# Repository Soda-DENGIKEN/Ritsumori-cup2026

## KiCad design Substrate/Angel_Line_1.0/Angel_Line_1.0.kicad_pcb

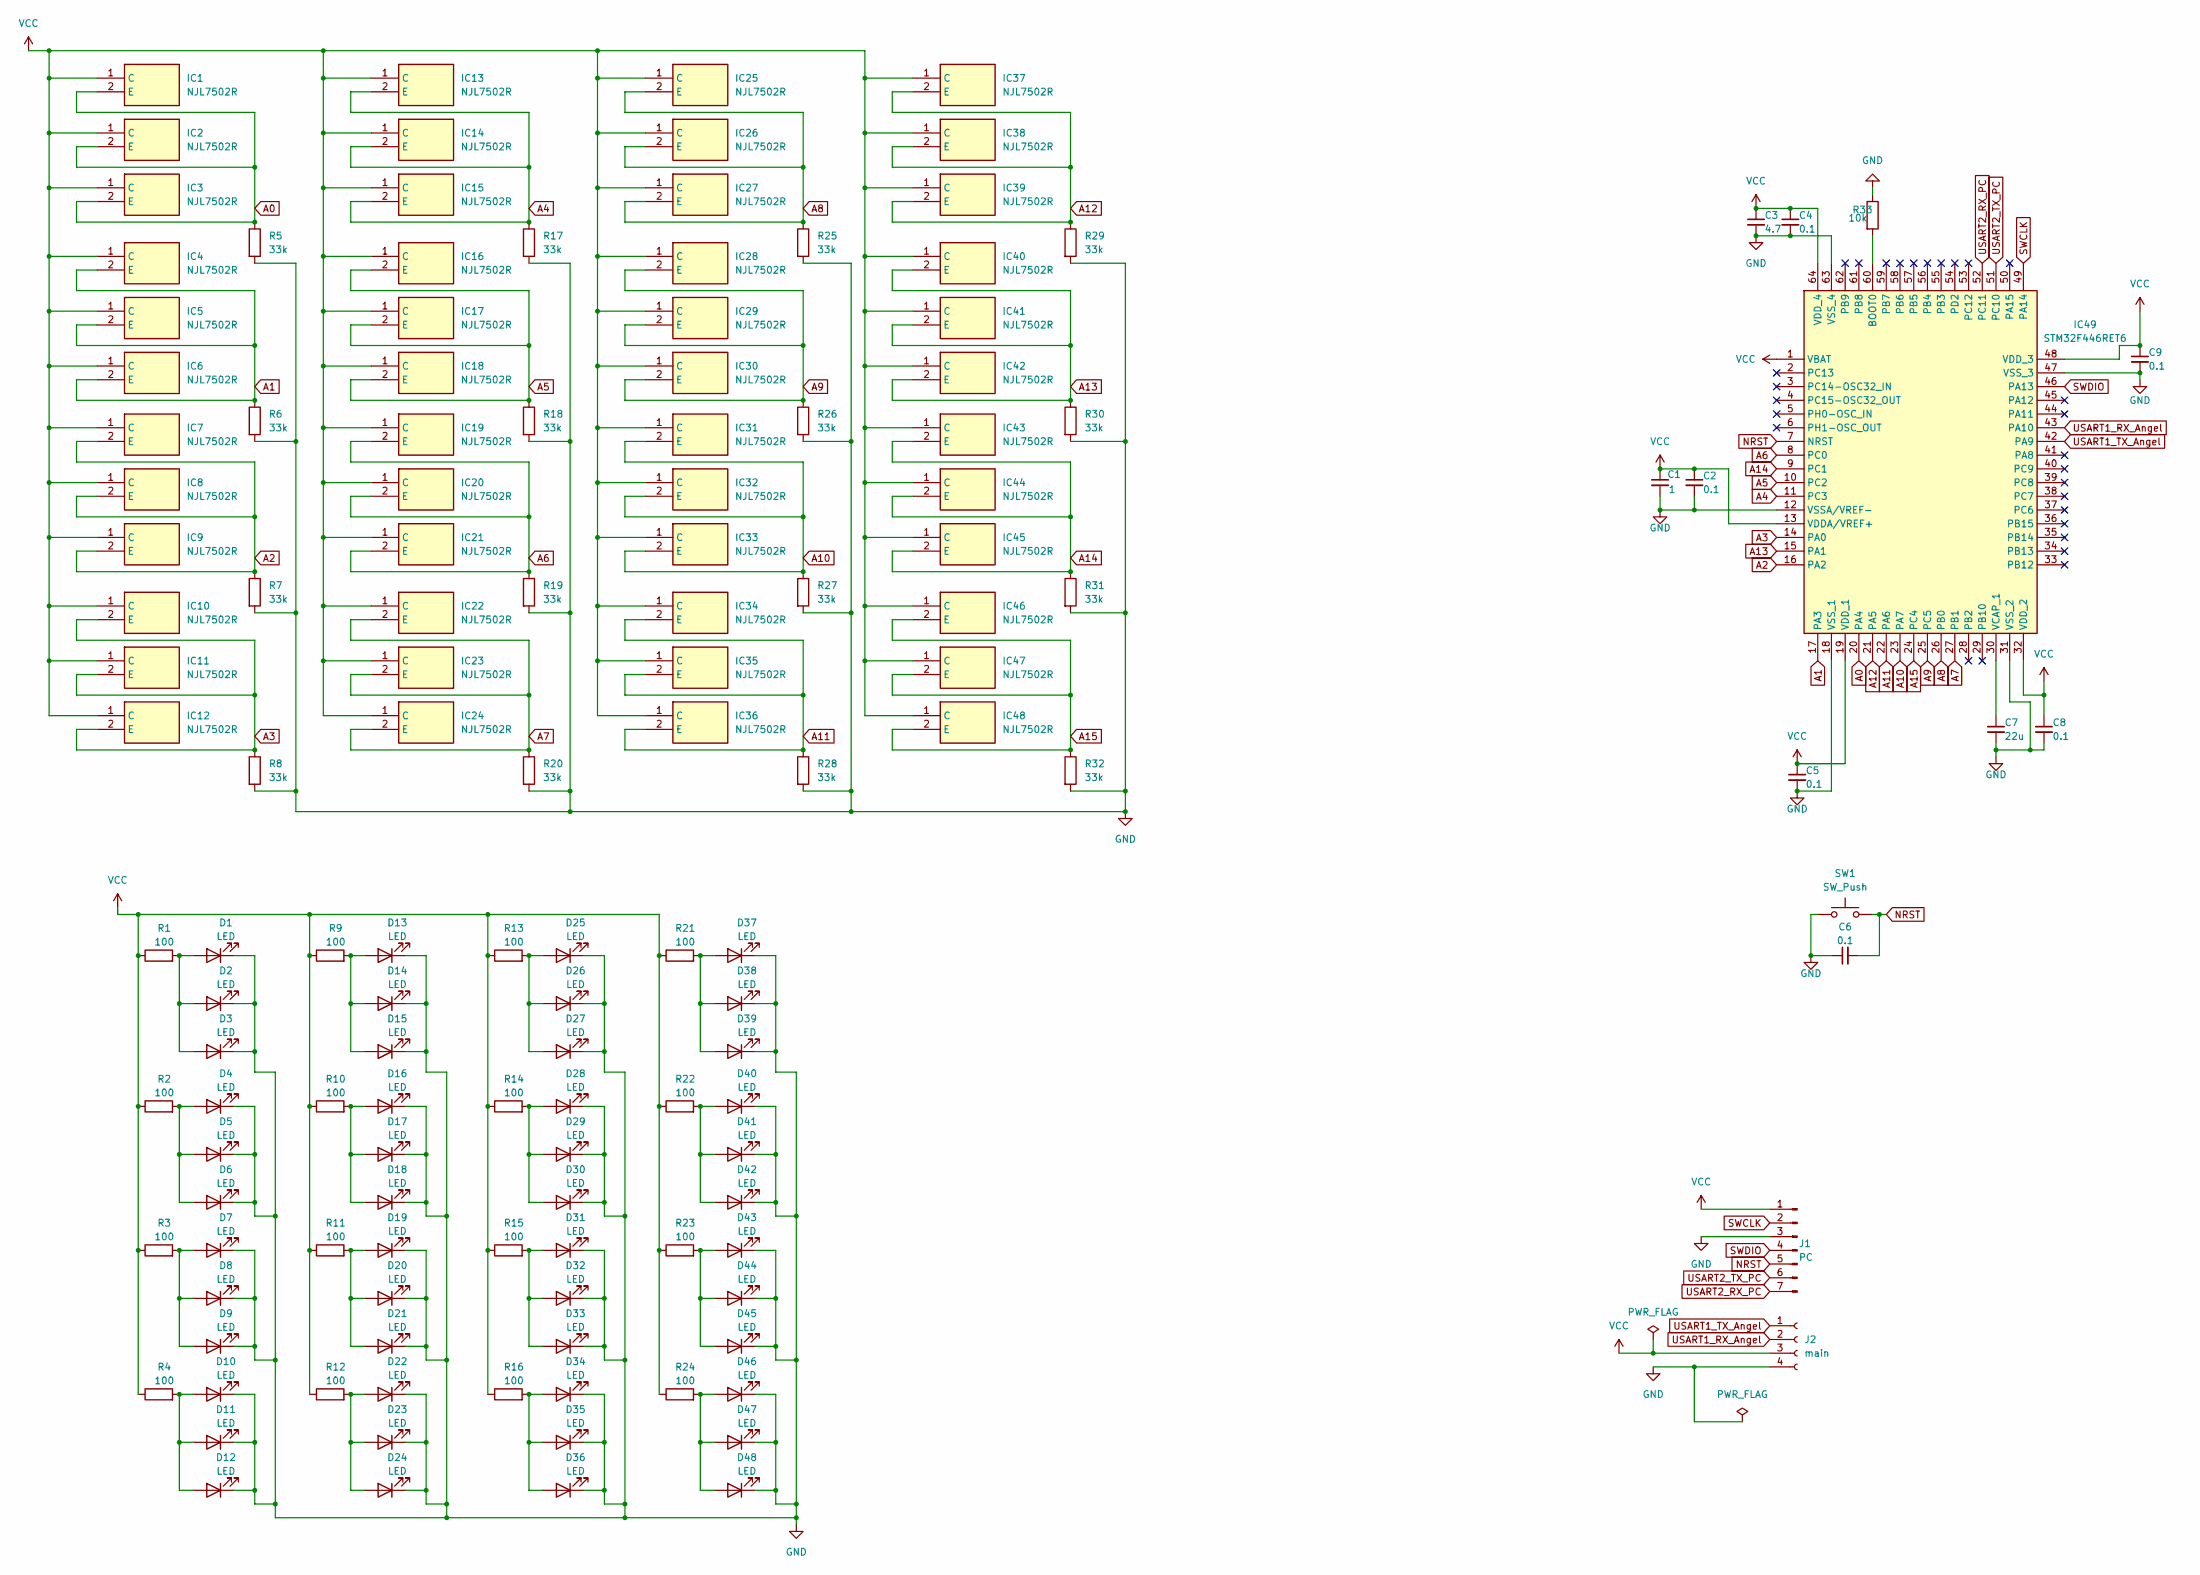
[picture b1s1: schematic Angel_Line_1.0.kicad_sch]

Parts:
C1: 1; C_0603_1608Metric
C2, C4, C5, C6, C8, C9: 0.1; C_0603_1608Metric
C3: 4.7; C_0603_1608Metric
C7: 22u; C_0603_1608Metric
D1, D2, D3, D4, D5, D6, D7, D8, D9, D10, D11, D12, D13, D14, D15, D16, D17, D18, D19, D20, D21, D22, D23, D24, D25, D26, D27, D28, D29, D30, D31, D32, D33, D34, D35, D36, D37, D38, D39, D40, D41, D42, D43, D44, D45, D46, D47, D48: LED; LED_0603_1608Metric_Pad1.05x0.95mm_HandSolder
IC1, IC2, IC3, IC4, IC5, IC6, IC7, IC8, IC9, IC10, IC11, IC12, IC13, IC14, IC15, IC16, IC17, IC18, IC19, IC20, IC21, IC22, IC23, IC24, IC25, IC26, IC27, IC28, IC29, IC30, IC31, IC32, IC33, IC34, IC35, IC36, IC37, IC38, IC39, IC40, IC41, IC42, IC43, IC44, IC45, IC46, IC47, IC48: NJL7502R; Manufacturer_Part_Number NJL7502R
IC49: STM32F446RET6; LQFP-64_10x10mm_P0.5mm; Manufacturer_Part_Number STM32F446RET6; Mouser Part Number 511-STM32F446RET6
J1: PC; PinHeader_1x07_P2.54mm_Vertical
J2: main; JST_XH_B4B-XH-A_1x04_P2.50mm_Vertical
R1, R2, R3, R4, R9, R10, R11, R12, R13, R14, R15, R16, R21, R22, R23, R24: 100; R_0603_1608Metric_Pad0.98x0.95mm_HandSolder
R5, R6, R7, R8, R17, R18, R19, R20, R25, R26, R27, R28, R29, R30, R31, R32: 33k; R_0603_1608Metric_Pad0.98x0.95mm_HandSolder
R33: 10k; R_0603_1608Metric
SW1: SW_Push; SKRPABE010

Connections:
A0: IC1.2 (E), IC2.2 (E), IC3.2 (E), IC49.20 (PA4), R5.1
A1: IC4.2 (E), IC5.2 (E), IC6.2 (E), IC49.17 (PA3), R6.1
A2: IC7.2 (E), IC8.2 (E), IC9.2 (E), IC49.16 (PA2), R7.1
A3: IC10.2 (E), IC11.2 (E), IC12.2 (E), IC49.14 (PA0), R8.1
A4: IC13.2 (E), IC14.2 (E), IC15.2 (E), IC49.11 (PC3), R17.1
A5: IC16.2 (E), IC17.2 (E), IC18.2 (E), IC49.10 (PC2), R18.1
A6: IC19.2 (E), IC20.2 (E), IC21.2 (E), IC49.8 (PC0), R19.1
A7: IC22.2 (E), IC23.2 (E), IC24.2 (E), IC49.27 (PB1), R20.1
A8: IC25.2 (E), IC26.2 (E), IC27.2 (E), IC49.26 (PB0), R25.1
A9: IC28.2 (E), IC29.2 (E), IC30.2 (E), IC49.25 (PC5), R26.1
A10: IC31.2 (E), IC32.2 (E), IC33.2 (E), IC49.23 (PA7), R27.1
A11: IC34.2 (E), IC35.2 (E), IC36.2 (E), IC49.22 (PA6), R28.1
A12: IC37.2 (E), IC38.2 (E), IC39.2 (E), IC49.21 (PA5), R29.1
A13: IC40.2 (E), IC41.2 (E), IC42.2 (E), IC49.15 (PA1), R30.1
A14: IC43.2 (E), IC44.2 (E), IC45.2 (E), IC49.9 (PC1), R31.1
A15: IC46.2 (E), IC47.2 (E), IC48.2 (E), IC49.24 (PC4), R32.1
GND: C1.2, C2.2, C3.2, C4.2, C5.2, C6.1, C7.2, C8.2, C9.2, D1.1 (K), D2.1 (K), D3.1 (K), D4.1 (K), D5.1 (K), D6.1 (K), D7.1 (K), D8.1 (K), D9.1 (K), D10.1 (K), D11.1 (K), D12.1 (K), D13.1 (K), D14.1 (K), D15.1 (K), D16.1 (K), D17.1 (K), D18.1 (K), D19.1 (K), D20.1 (K), D21.1 (K), D22.1 (K), D23.1 (K), D24.1 (K), D25.1 (K), D26.1 (K), D27.1 (K), D28.1 (K), D29.1 (K), D30.1 (K), D31.1 (K), D32.1 (K), D33.1 (K), D34.1 (K), D35.1 (K), D36.1 (K), D37.1 (K), D38.1 (K), D39.1 (K), D40.1 (K), D41.1 (K), D42.1 (K), D43.1 (K), D44.1 (K), D45.1 (K), D46.1 (K), D47.1 (K), D48.1 (K), IC49.12 (VSSA/VREF-), IC49.18 (VSS_1), IC49.31 (VSS_2), IC49.47 (VSS_3), IC49.63 (VSS_4), J1.3, J2.4, R5.2, R6.2, R7.2, R8.2, R17.2, R18.2, R19.2, R20.2, R25.2, R26.2, R27.2, R28.2, R29.2, R30.2, R31.2, R32.2, R33.1, SW1.1
NRST: C6.2, IC49.7 (NRST), J1.5, SW1.2
unnamed: D1.2 (A), D2.2 (A), D3.2 (A), R1.2
unnamed: D4.2 (A), D5.2 (A), D6.2 (A), R2.2
unnamed: D7.2 (A), D8.2 (A), D9.2 (A), R3.2
unnamed: D10.2 (A), D11.2 (A), D12.2 (A), R4.2
unnamed: D13.2 (A), D14.2 (A), D15.2 (A), R9.2
unnamed: D16.2 (A), D17.2 (A), D18.2 (A), R10.2
unnamed: D19.2 (A), D20.2 (A), D21.2 (A), R11.2
unnamed: D22.2 (A), D23.2 (A), D24.2 (A), R12.2
unnamed: D25.2 (A), D26.2 (A), D27.2 (A), R13.2
unnamed: D28.2 (A), D29.2 (A), D30.2 (A), R14.2
unnamed: D31.2 (A), D32.2 (A), D33.2 (A), R15.2
unnamed: D34.2 (A), D35.2 (A), D36.2 (A), R16.2
unnamed: D37.2 (A), D38.2 (A), D39.2 (A), R21.2
unnamed: D40.2 (A), D41.2 (A), D42.2 (A), R22.2
unnamed: D43.2 (A), D44.2 (A), D45.2 (A), R23.2
unnamed: D46.2 (A), D47.2 (A), D48.2 (A), R24.2
unnamed: IC49.60 (BOOT0), R33.2
unnamed: C7.1, IC49.30 (VCAP_1)
SWCLK: IC49.49 (PA14), J1.2
SWDIO: IC49.46 (PA13), J1.4
USART1_RX_Angel: IC49.43 (PA10), J2.2
USART1_TX_Angel: IC49.42 (PA9), J2.1
USART2_RX_PC: IC49.52 (PC11), J1.7
USART2_TX_PC: IC49.51 (PC10), J1.6
VCC: C1.1, C2.1, C3.1, C4.1, C5.1, C8.1, C9.1, IC1.1 (C), IC2.1 (C), IC3.1 (C), IC4.1 (C), IC5.1 (C), IC6.1 (C), IC7.1 (C), IC8.1 (C), IC9.1 (C), IC10.1 (C), IC11.1 (C), IC12.1 (C), IC13.1 (C), IC14.1 (C), IC15.1 (C), IC16.1 (C), IC17.1 (C), IC18.1 (C), IC19.1 (C), IC20.1 (C), IC21.1 (C), IC22.1 (C), IC23.1 (C), IC24.1 (C), IC25.1 (C), IC26.1 (C), IC27.1 (C), IC28.1 (C), IC29.1 (C), IC30.1 (C), IC31.1 (C), IC32.1 (C), IC33.1 (C), IC34.1 (C), IC35.1 (C), IC36.1 (C), IC37.1 (C), IC38.1 (C), IC39.1 (C), IC40.1 (C), IC41.1 (C), IC42.1 (C), IC43.1 (C), IC44.1 (C), IC45.1 (C), IC46.1 (C), IC47.1 (C), IC48.1 (C), IC49.1 (VBAT), IC49.13 (VDDA/VREF+), IC49.19 (VDD_1), IC49.32 (VDD_2), IC49.48 (VDD_3), IC49.64 (VDD_4), J1.1, J2.3, R1.1, R2.1, R3.1, R4.1, R9.1, R10.1, R11.1, R12.1, R13.1, R14.1, R15.1, R16.1, R21.1, R22.1, R23.1, R24.1

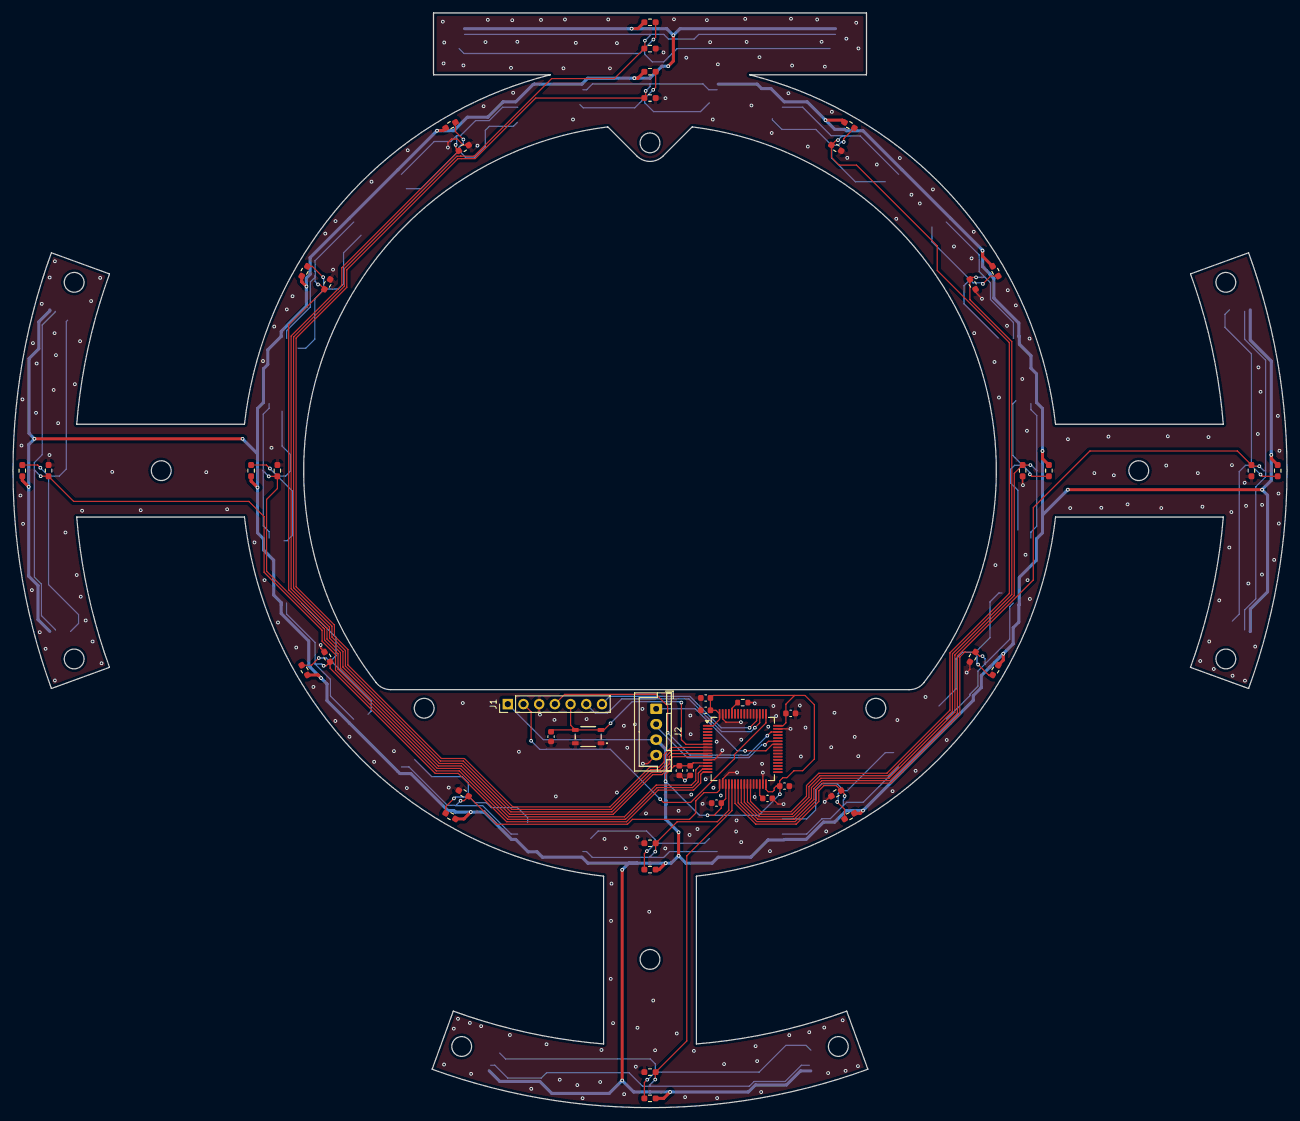
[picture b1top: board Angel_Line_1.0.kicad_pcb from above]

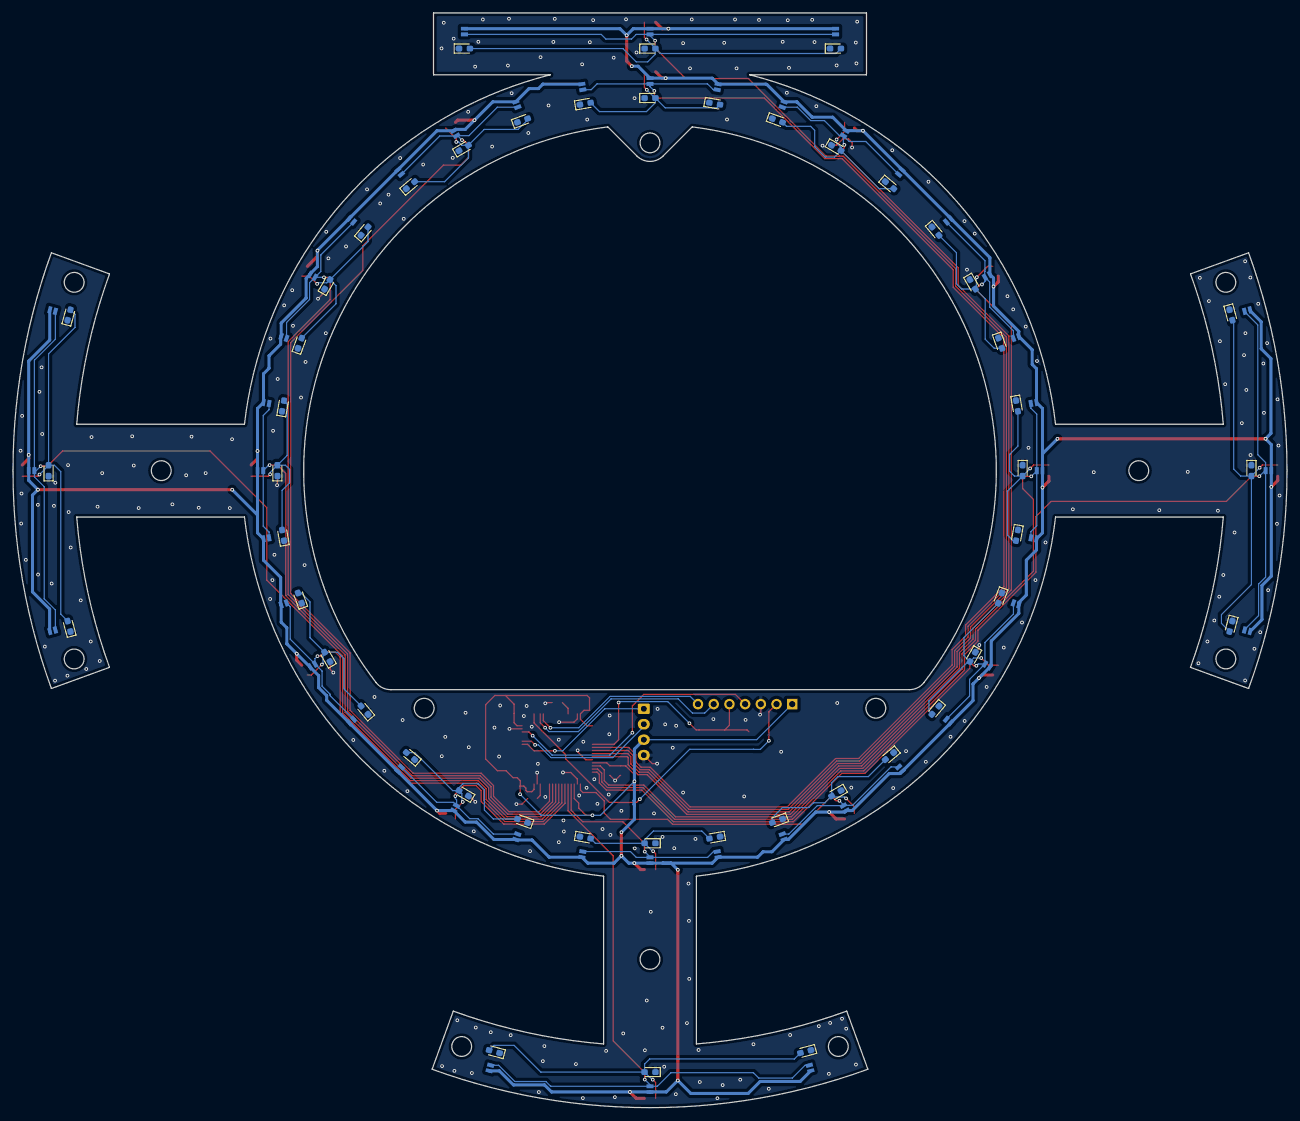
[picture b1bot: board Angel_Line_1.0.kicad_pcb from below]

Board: 2 copper layers, 206.0 x 177.0 mm, 142 parts (96 on the bottom side), 43 nets.

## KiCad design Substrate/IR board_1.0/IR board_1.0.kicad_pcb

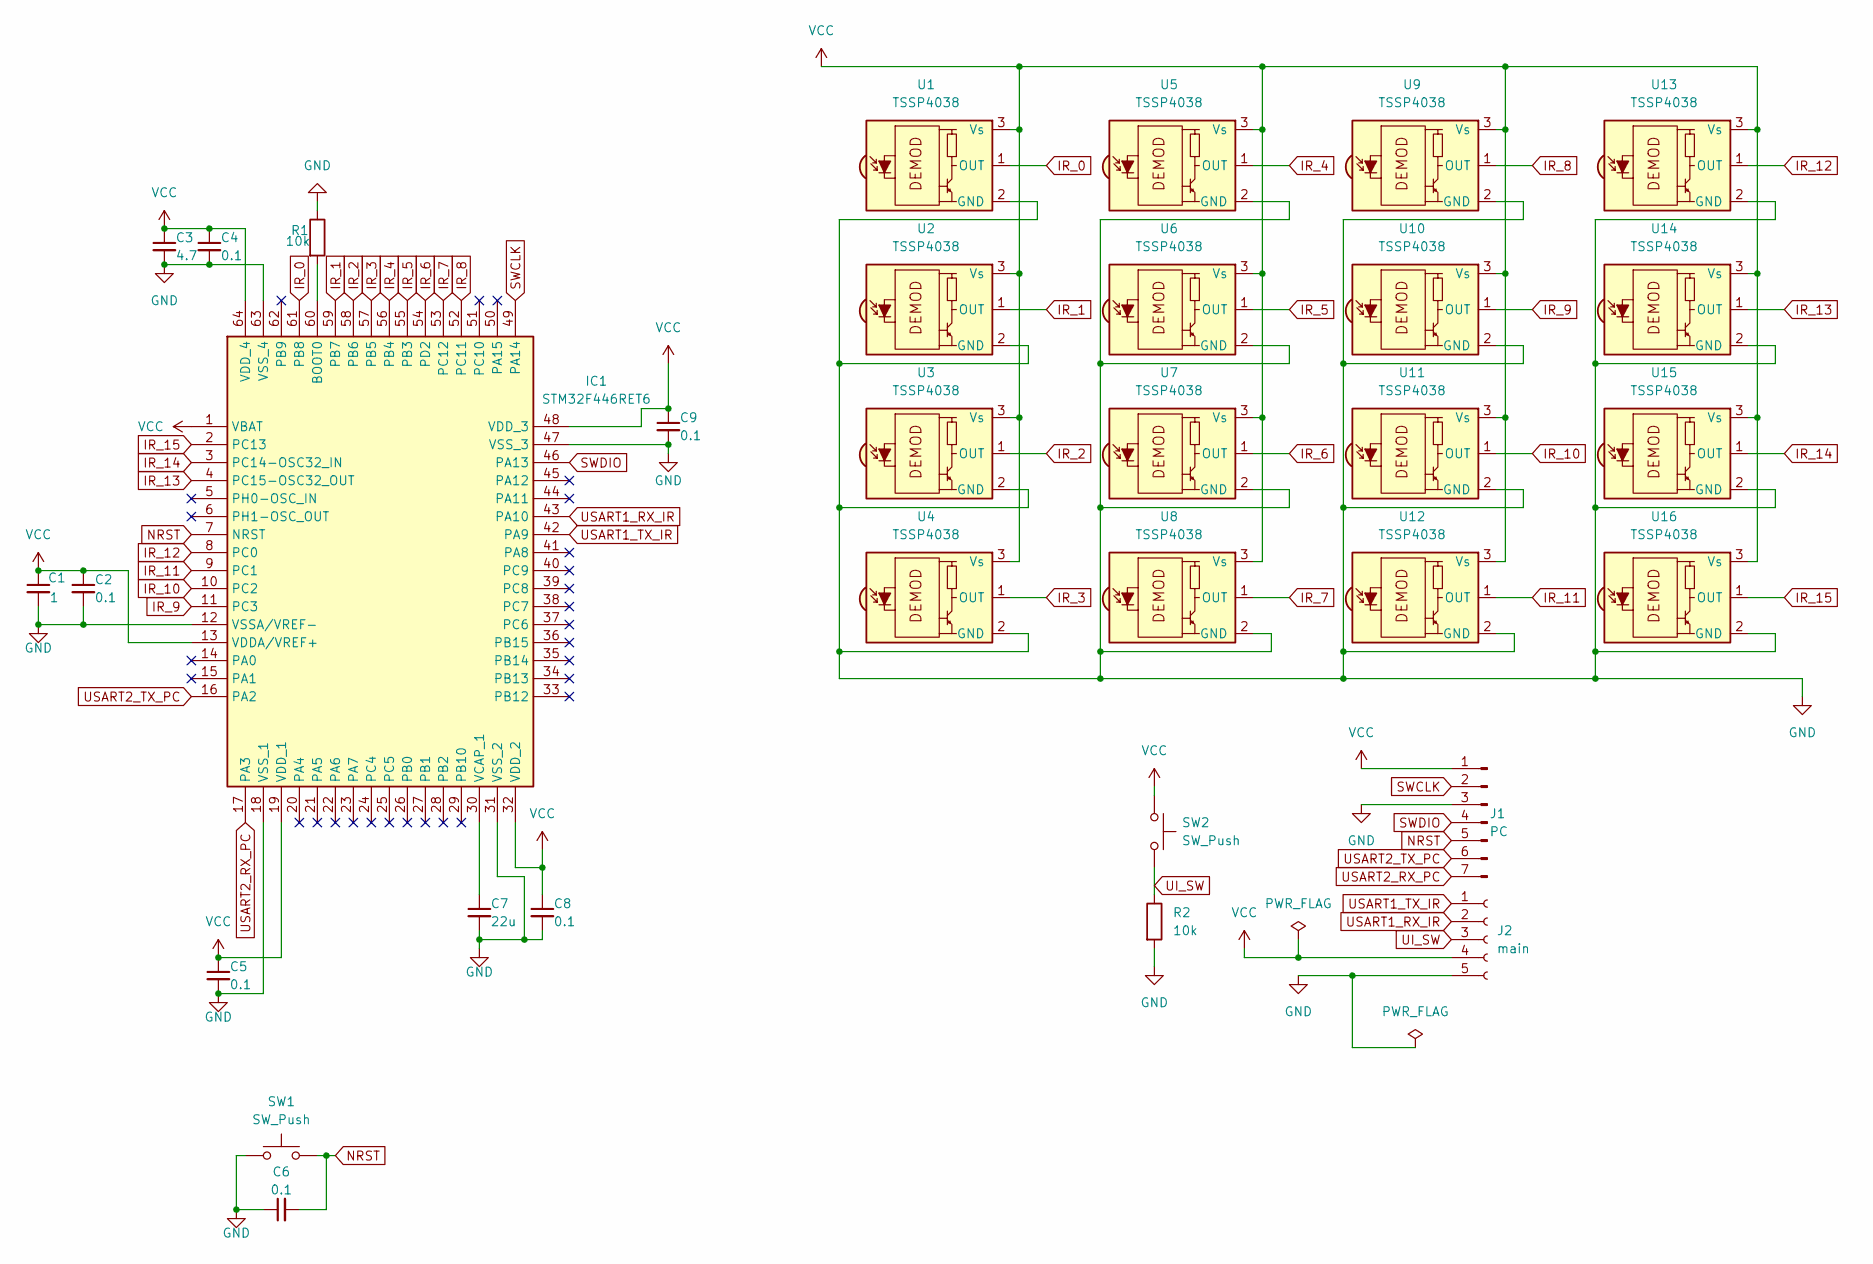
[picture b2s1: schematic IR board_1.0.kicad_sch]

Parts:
C1: 1; C_0603_1608Metric
C2, C4, C5, C6, C8, C9: 0.1; C_0603_1608Metric
C3: 4.7; C_0603_1608Metric
C7: 22u; C_0603_1608Metric
IC1: STM32F446RET6; LQFP-64_10x10mm_P0.5mm; Manufacturer_Part_Number STM32F446RET6; Mouser Part Number 511-STM32F446RET6
J1: PC; PinHeader_1x07_P2.54mm_Horizontal
J2: main; JST_XH_B5B-XH-A_1x05_P2.50mm_Vertical
R1, R2: 10k; R_0603_1608Metric
SW1: SW_Push; SKRPABE010
SW2: SW_Push; TVGP01-G73BB
U1, U2, U3, U4, U5, U6, U7, U8, U9, U10, U11, U12, U13, U14, U15, U16: TSSP4038; Vishay_MINICAST-3Pin

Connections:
GND: C1.2, C2.2, C3.2, C4.2, C5.2, C6.1, C7.2, C8.2, C9.2, IC1.12 (VSSA/VREF-), IC1.18 (VSS_1), IC1.31 (VSS_2), IC1.47 (VSS_3), IC1.63 (VSS_4), J1.3, J2.5, R1.1, R2.2, SW1.1, U1.2 (GND), U2.2 (GND), U3.2 (GND), U4.2 (GND), U5.2 (GND), U6.2 (GND), U7.2 (GND), U8.2 (GND), U9.2 (GND), U10.2 (GND), U11.2 (GND), U12.2 (GND), U13.2 (GND), U14.2 (GND), U15.2 (GND), U16.2 (GND); also elsewhere on the board
IR_0: IC1.61 (PB8), U1.1 (OUT)
IR_1: IC1.59 (PB7), U2.1 (OUT)
IR_2: IC1.58 (PB6), U3.1 (OUT)
IR_3: IC1.57 (PB5), U4.1 (OUT)
IR_4: IC1.56 (PB4), U5.1 (OUT)
IR_5: IC1.55 (PB3), U6.1 (OUT)
IR_6: IC1.54 (PD2), U7.1 (OUT)
IR_7: IC1.53 (PC12), U8.1 (OUT)
IR_8: IC1.52 (PC11), U9.1 (OUT)
IR_9: IC1.11 (PC3), U10.1 (OUT)
IR_10: IC1.10 (PC2), U11.1 (OUT)
IR_11: IC1.9 (PC1), U12.1 (OUT)
IR_12: IC1.8 (PC0), U13.1 (OUT)
IR_13: IC1.4 (PC15-OSC32_OUT), U14.1 (OUT)
IR_14: IC1.3 (PC14-OSC32_IN), U15.1 (OUT)
IR_15: IC1.2 (PC13), U16.1 (OUT)
NRST: C6.2, IC1.7 (NRST), J1.5, SW1.2
unnamed: IC1.60 (BOOT0), R1.2
unnamed: C7.1, IC1.30 (VCAP_1)
SWCLK: IC1.49 (PA14), J1.2
SWDIO: IC1.46 (PA13), J1.4
UI_SW: J2.3, R2.1, SW2.2
USART1_RX_IR: IC1.43 (PA10), J2.2
USART1_TX_IR: IC1.42 (PA9), J2.1
USART2_RX_PC: IC1.17 (PA3), J1.7
USART2_TX_PC: IC1.16 (PA2), J1.6
VCC: C1.1, C2.1, C3.1, C4.1, C5.1, C8.1, C9.1, IC1.1 (VBAT), IC1.13 (VDDA/VREF+), IC1.19 (VDD_1), IC1.32 (VDD_2), IC1.48 (VDD_3), IC1.64 (VDD_4), J1.1, J2.4, SW2.1, U1.3 (Vs), U2.3 (Vs), U3.3 (Vs), U4.3 (Vs), U5.3 (Vs), U6.3 (Vs), U7.3 (Vs), U8.3 (Vs), U9.3 (Vs), U10.3 (Vs), U11.3 (Vs), U12.3 (Vs), U13.3 (Vs), U14.3 (Vs), U15.3 (Vs), U16.3 (Vs); also elsewhere on the board

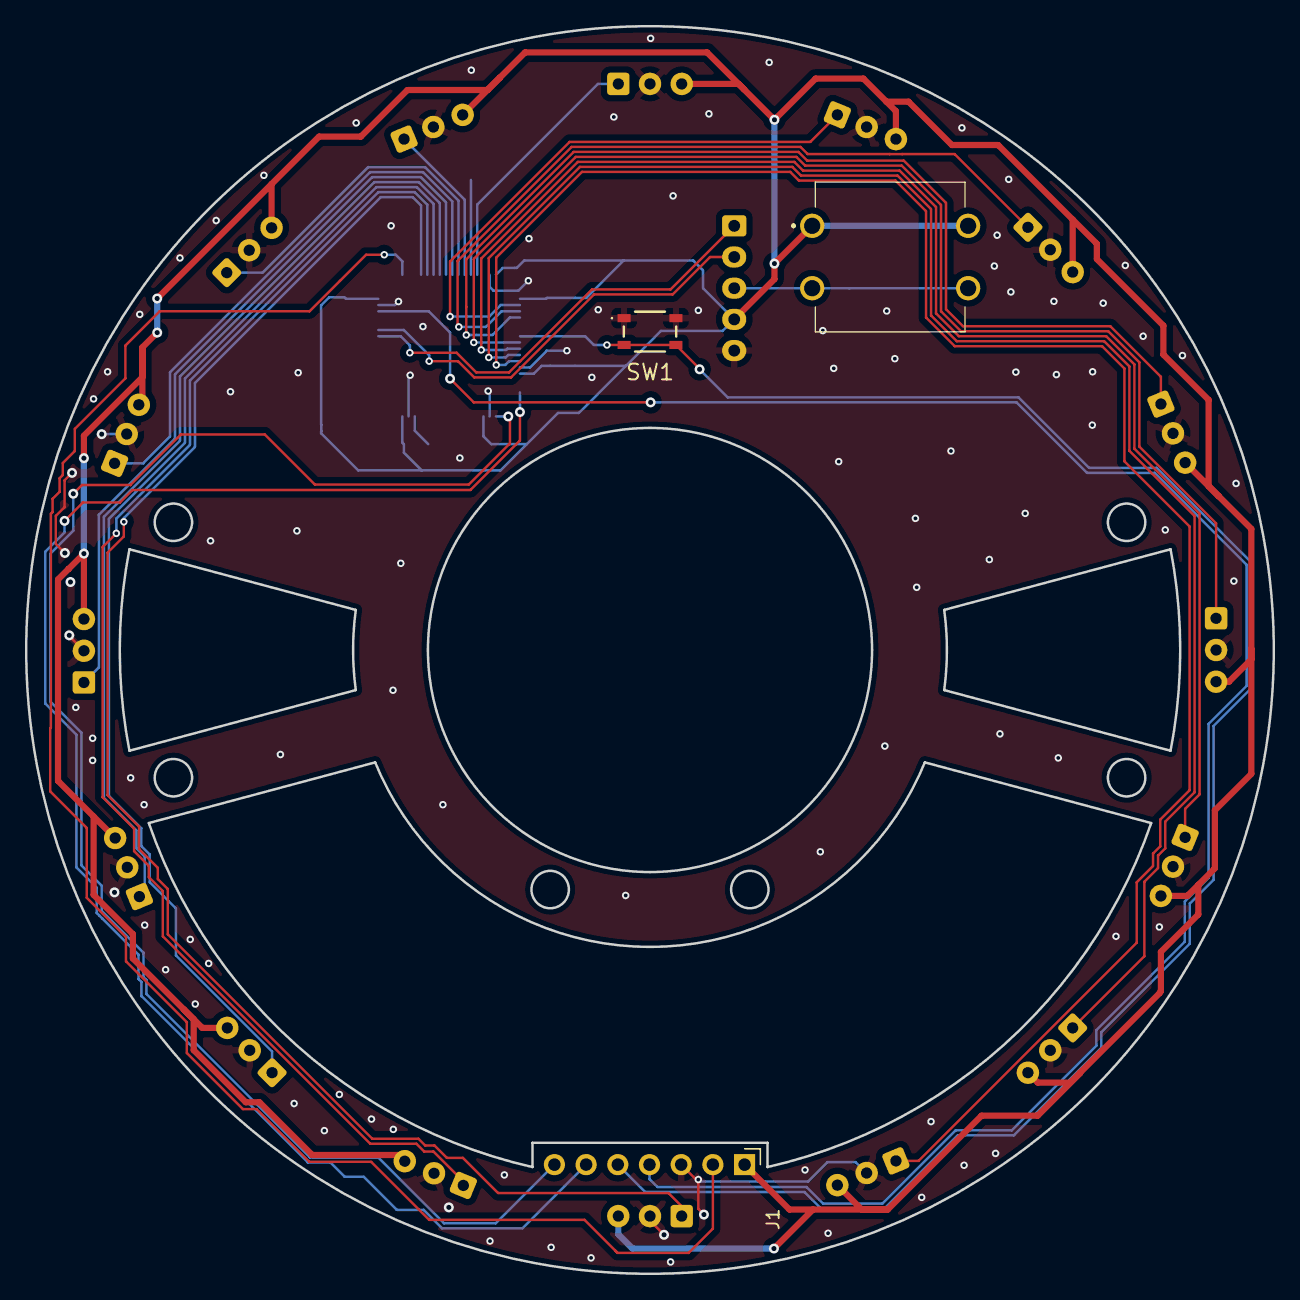
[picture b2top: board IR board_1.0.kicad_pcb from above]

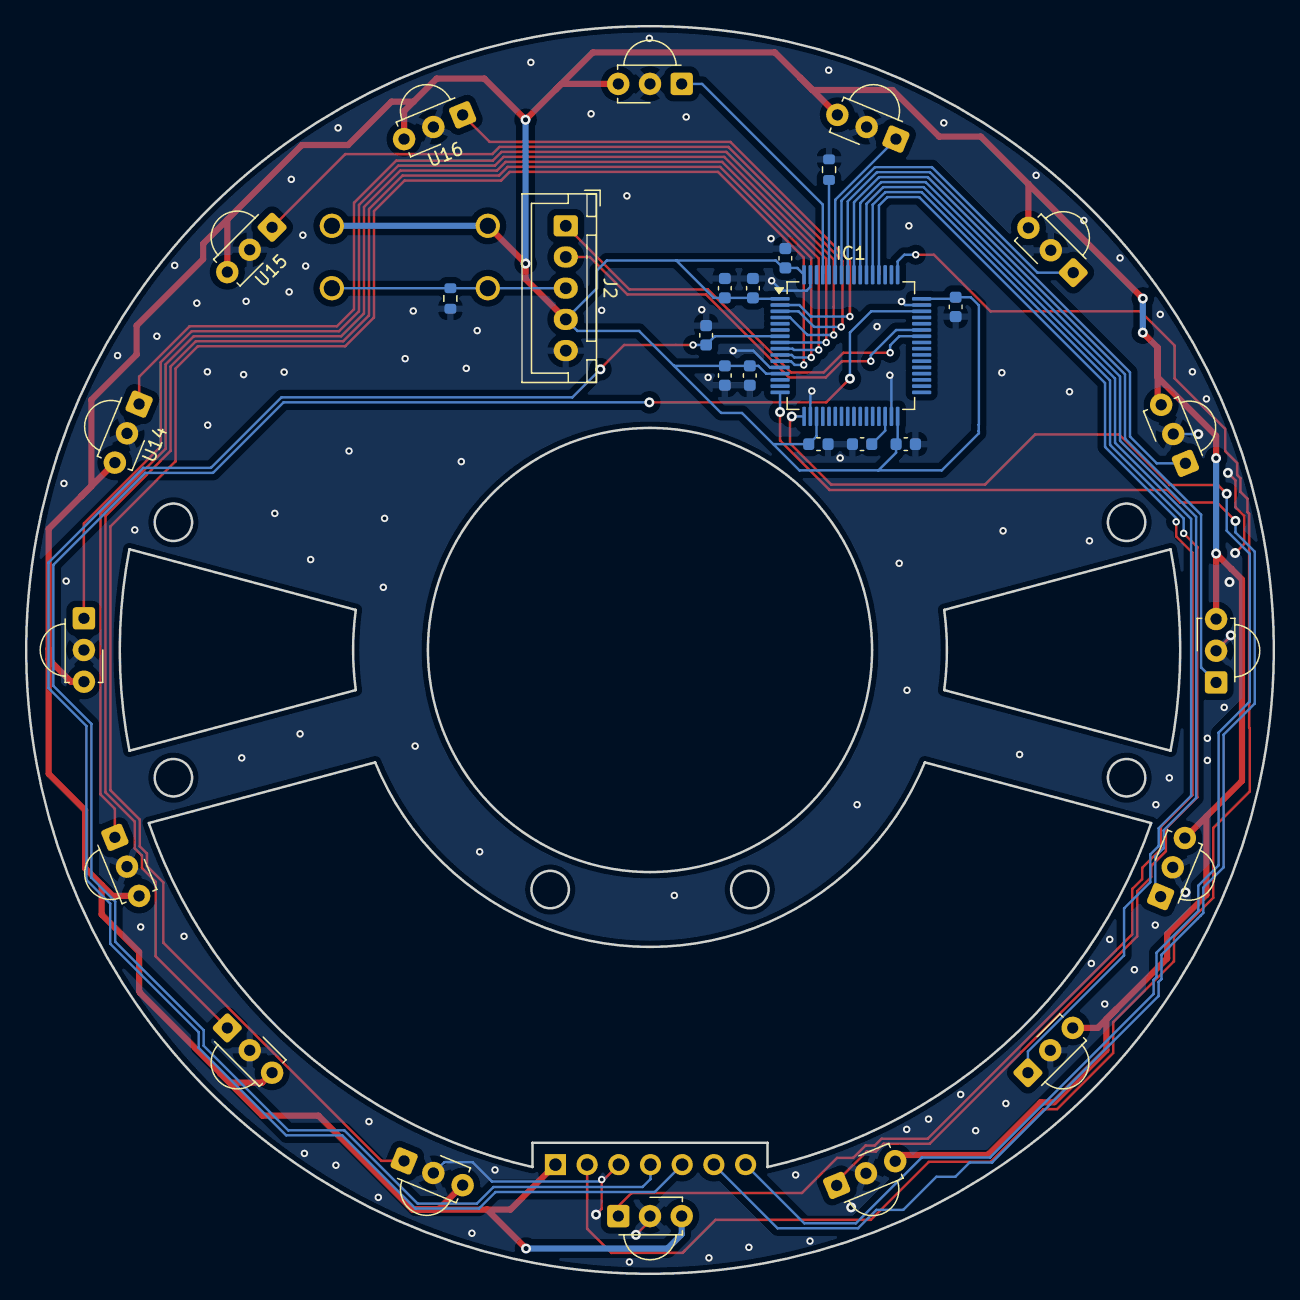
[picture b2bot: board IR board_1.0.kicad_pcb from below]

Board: 2 copper layers, 100.0 x 100.0 mm, 33 parts (30 on the bottom side), 28 nets.

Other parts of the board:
C8#2: 0.1; C_0603_1608Metric

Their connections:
GND: C8#2.2; also elsewhere on the board
VCC: C8#2.1; also elsewhere on the board

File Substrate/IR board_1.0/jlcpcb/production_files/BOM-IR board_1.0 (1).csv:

Comment,Designator,Footprint,LCSC,Quantity
0.1,"C2,C4,C5,C6,C8,C9",C_0603_1608Metric,C14663,6
1,C1,C_0603_1608Metric,C15849,1
10k,"R1,R2",R_0603_1608Metric,C25804,2
22u,C7,C_0603_1608Metric,C59461,1
4.7,C3,C_0603_1608Metric,C19666,1
STM32F446RET6,IC1,LQFP-64_10x10mm_P0.5mm,C69336,1
TSSP4038,U2,Vishay_MINICAST-3Pin,,1
TSSP4038,U3,Vishay_MINICAST-3Pin,,1
TSSP4038,U8,Vishay_MINICAST-3Pin,,1
SW_Push,SW2,TVGP01-G73BB,,1
TSSP4038,U12,Vishay_MINICAST-3Pin,,1
TSSP4038,U10,Vishay_MINICAST-3Pin,,1
TSSP4038,U9,Vishay_MINICAST-3Pin,,1
TSSP4038,U5,Vishay_MINICAST-3Pin,,1
TSSP4038,U14,Vishay_MINICAST-3Pin,,1
TSSP4038,U6,Vishay_MINICAST-3Pin,,1
TSSP4038,U4,Vishay_MINICAST-3Pin,,1
TSSP4038,U11,Vishay_MINICAST-3Pin,,1
TSSP4038,U7,Vishay_MINICAST-3Pin,,1
TSSP4038,U16,Vishay_MINICAST-3Pin,,1
TSSP4038,U15,Vishay_MINICAST-3Pin,,1
TSSP4038,U13,Vishay_MINICAST-3Pin,,1
TSSP4038,U1,Vishay_MINICAST-3Pin,,1
PC,J1,PinHeader_1x07_P2.54mm_Horizontal,,1
main,J2,JST_XH_B5B-XH-A_1x05_P2.50mm_Vertical,,1
SW_Push,NRST,SKRPABE010,,1

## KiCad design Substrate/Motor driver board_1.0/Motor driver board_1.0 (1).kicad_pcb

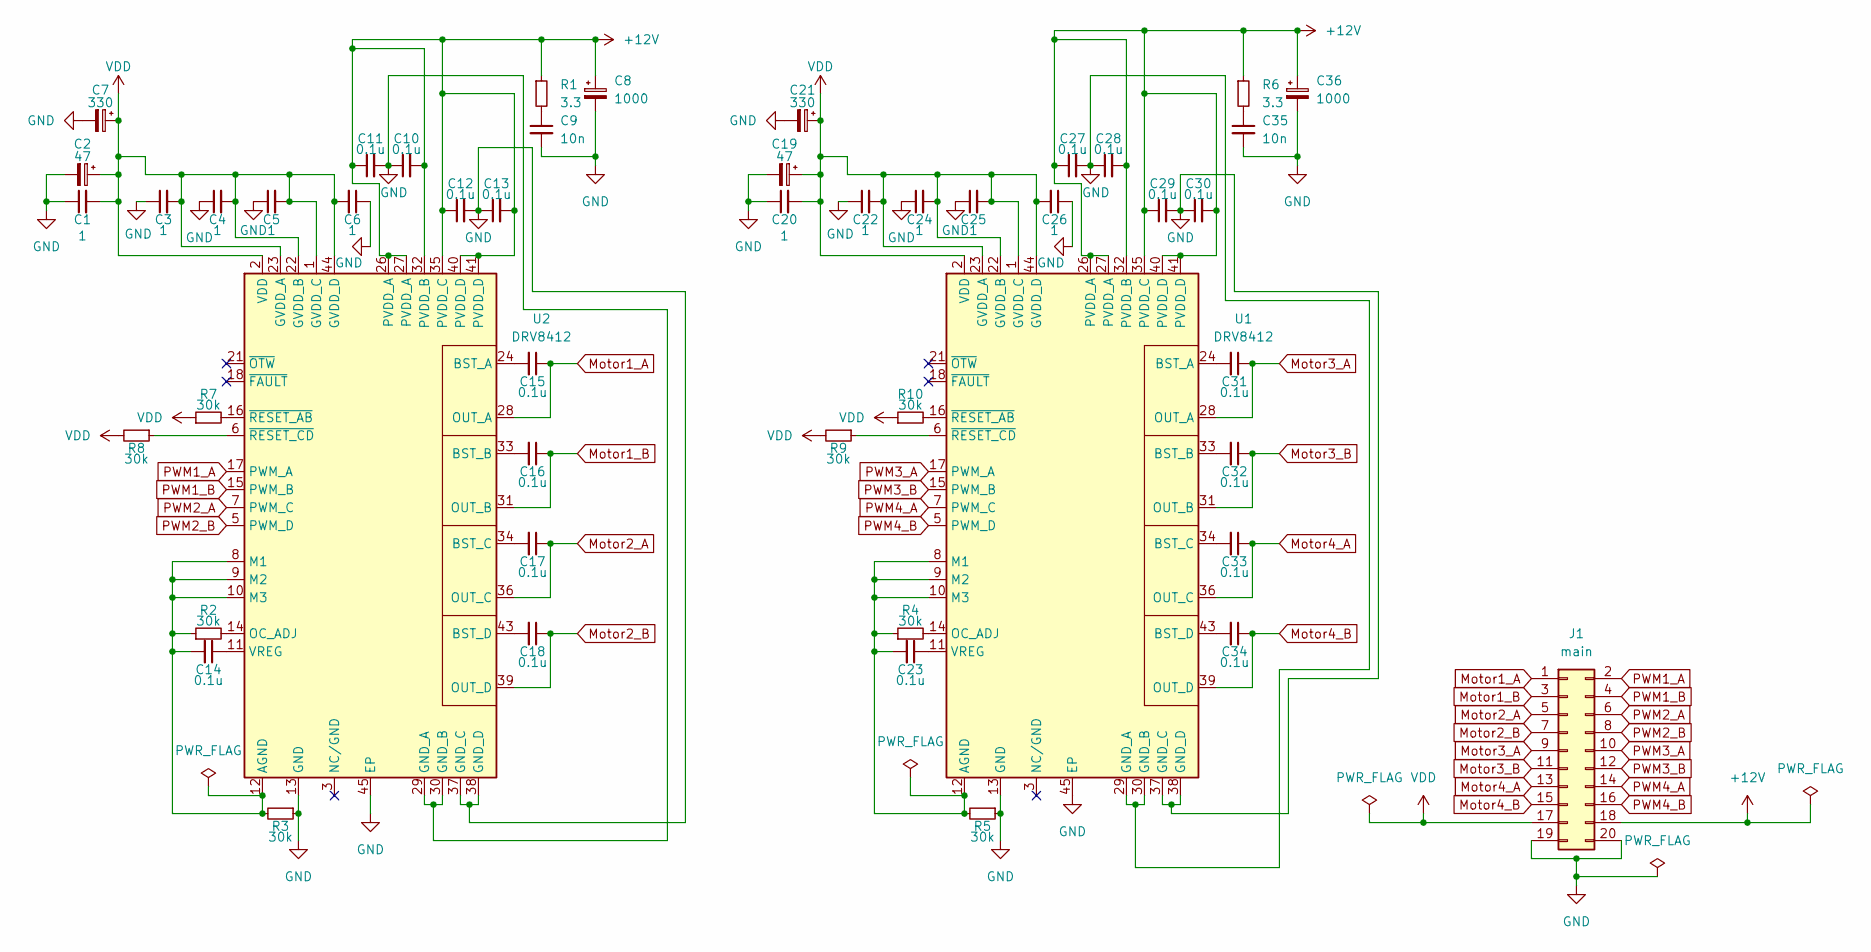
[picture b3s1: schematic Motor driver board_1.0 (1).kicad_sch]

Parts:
C1, C3, C4, C5, C6, C20, C22, C24, C25, C26: 1; C_0603_1608Metric
C2, C19: 47; CP_Radial_D6.3mm_P2.50mm
C7, C21: 330; CP_Radial_D10.0mm_P5.00mm
C8, C36: 1000; CP_Radial_D10.0mm_P5.00mm
C9, C35: 10n; C_0603_1608Metric
C10, C11, C12, C13, C14, C15, C16, C17, C18, C23, C27, C28, C29, C30, C31, C32, C33, C34: 0.1u; C_0603_1608Metric
J1: main; PinSocket_2x10_P2.54mm_Vertical
R1, R6: 3.3; R_0603_1608Metric
R2, R3, R4, R5, R7, R8, R9, R10: 30k; R_0603_1608Metric
U1, U2: DRV8412; HTSSOP-44-1EP_6.1x14mm_P0.635mm_EP5.2x14mm_Mask4.31x8.26mm_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

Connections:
+12V: C8.1, C10.2, C11.1, C12.1, C13.2, C27.1, C28.2, C29.1, C30.2, C36.1, J1.18, R1.1, R6.1, U1.26 (PVDD_A), U1.27 (PVDD_A), U1.32 (PVDD_B), U1.35 (PVDD_C), U1.40 (PVDD_D), U1.41 (PVDD_D), U2.26 (PVDD_A), U2.27 (PVDD_A), U2.32 (PVDD_B), U2.35 (PVDD_C), U2.40 (PVDD_D), U2.41 (PVDD_D)
GND: C1.1, C2.2, C3.1, C4.1, C5.1, C6.1, C7.2, C8.2, C9.2, C10.1, C11.2, C12.2, C13.1, C19.2, C20.1, C21.2, C22.1, C24.1, C25.1, C26.1, C27.2, C28.1, C29.2, C30.1, C35.2, C36.2, J1.19, J1.20, R3.1, R5.1, U1.13 (GND), U1.29 (GND_A), U1.30 (GND_B), U1.37 (GND_C), U1.38 (GND_D), U1.45 (EP), U2.13 (GND), U2.29 (GND_A), U2.30 (GND_B), U2.37 (GND_C), U2.38 (GND_D), U2.45 (EP)
Motor1_A: C15.1, J1.1, U2.28 (OUT_A)
Motor1_B: C16.1, J1.3, U2.31 (OUT_B)
Motor2_A: C17.1, J1.5, U2.36 (OUT_C)
Motor2_B: C18.1, J1.7, U2.39 (OUT_D)
Motor3_A: C31.1, J1.9, U1.28 (OUT_A)
Motor3_B: C32.1, J1.11, U1.31 (OUT_B)
Motor4_A: C33.1, J1.13, U1.36 (OUT_C)
Motor4_B: C34.1, J1.15, U1.39 (OUT_D)
unnamed: C9.1, R1.2
unnamed: C35.1, R6.2
unnamed: C23.2, R4.1, R5.2, U1.8 (M1), U1.9 (M2), U1.10 (M3), U1.12 (AGND)
unnamed: C31.2, U1.24 (BST_A)
unnamed: C32.2, U1.33 (BST_B)
unnamed: C33.2, U1.34 (BST_C)
unnamed: C34.2, U1.43 (BST_D)
unnamed: R4.2, U1.14 (OC_ADJ)
unnamed: C23.1, U1.11 (VREG)
unnamed: R10.2, U1.16 (~RESET_AB)
unnamed: R9.1, U1.6 (~RESET_CD)
unnamed: C14.2, R2.1, R3.2, U2.8 (M1), U2.9 (M2), U2.10 (M3), U2.12 (AGND)
unnamed: C15.2, U2.24 (BST_A)
unnamed: C16.2, U2.33 (BST_B)
unnamed: C17.2, U2.34 (BST_C)
unnamed: C18.2, U2.43 (BST_D)
unnamed: R2.2, U2.14 (OC_ADJ)
unnamed: C14.1, U2.11 (VREG)
unnamed: R7.2, U2.16 (~RESET_AB)
unnamed: R8.1, U2.6 (~RESET_CD)
PWM1_A: J1.2, U2.17 (PWM_A)
PWM1_B: J1.4, U2.15 (PWM_B)
PWM2_A: J1.6, U2.7 (PWM_C)
PWM2_B: J1.8, U2.5 (PWM_D)
PWM3_A: J1.10, U1.17 (PWM_A)
PWM3_B: J1.12, U1.15 (PWM_B)
PWM4_A: J1.14, U1.7 (PWM_C)
PWM4_B: J1.16, U1.5 (PWM_D)
VDD: C1.2, C2.1, C3.2, C4.2, C5.2, C6.2, C7.1, C19.1, C20.2, C21.1, C22.2, C24.2, C25.2, C26.2, J1.17, R7.1, R8.2, R9.2, R10.1, U1.1 (GVDD_C), U1.2 (VDD), U1.22 (GVDD_B), U1.23 (GVDD_A), U1.44 (GVDD_D), U2.1 (GVDD_C), U2.2 (VDD), U2.22 (GVDD_B), U2.23 (GVDD_A), U2.44 (GVDD_D)

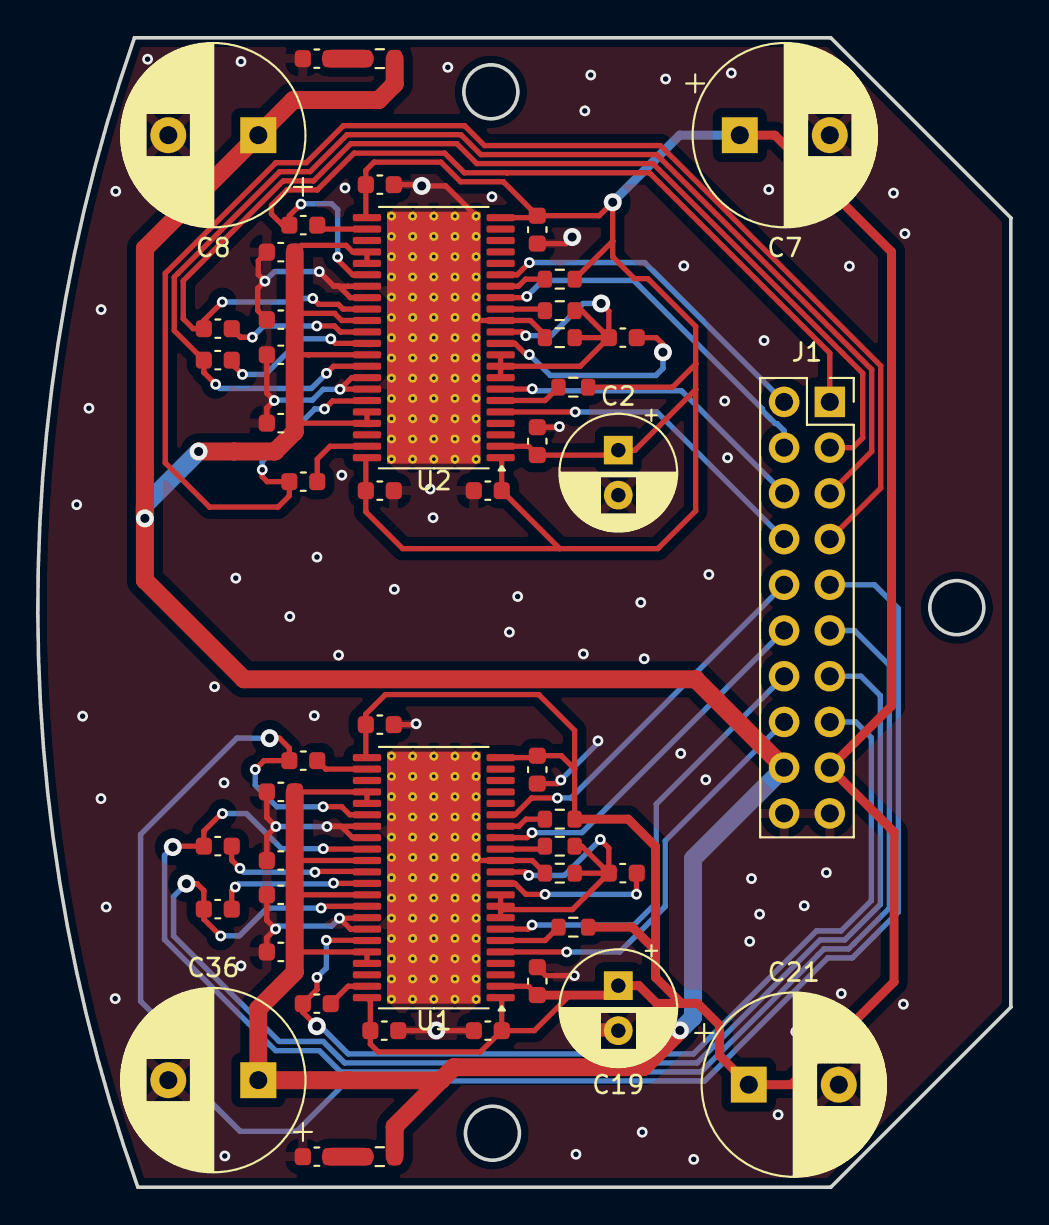
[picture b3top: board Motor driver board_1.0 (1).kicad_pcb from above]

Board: 2 copper layers, 54.1 x 63.9 mm, 49 parts (0 on the bottom side), 39 nets.
